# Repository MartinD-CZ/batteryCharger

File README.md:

# AVR-based universal battery charger

**UPDATE!** By popular request, I will be releasing a new version. Check [this post](http://embedblog.eu/?p=204) for more information.  
**UPDATE #2** I've abandoned the project, mostly because of time. What I have so far has been put into the 'unfinished-arduino' folder.

###### Overall
The charger is based on Atmega 328 (because it is dirt cheap) and utilizes its PWM to drive a FET, used as buck converter. There is also an 5110 LCD (again, less than 2 USD on Ebay) to show some basic menus and stuff. Most of the settings are adjustable on the go, so once you build and program it, you can use it without further reprogramming for all battery types and so on.

###### Batteries:
The charger supports all of the most used battery types - that is in my opinion NiCd, NiMH, Li-Ion and SLA. Li-Ion and SLA are charged in constant current-constant voltage mode, while Nickel based batteries are charged with constant current and terminated by about 5 methods (time out, overvoltage, overtemperature, -dV/dT, user termination). I have been using the charger for about a month before posting it here (tested everything except SLA, don’t have those on hand) and everything seems to work seamlessly. Maximum charging current is 3A, maximum charging voltage is almost Vin (that’s about 18V in my setup).

###### Discharge
The charger also comes with a discharge circuitry, used to:
	A) Measure battery capacity
	B) Discharge batteries before charging (useful with NiMH batteries to neutralize their memory effect)
The discharging current is fully adjustable from 0 to 3 amps, with undervoltage protection (again, fully adjustable). There is a small fan, which is automatically switched on when thermal power dissipation is bigger than 2 watts (you can change that, it depends on the size of your heatsink).

###### Power supply
Also in the menu you can find "constant C", "constant V" and "power supply" options. They provide you with simple power supply, useful for SOME applications. Because of the MCU limitations, the transient response time is relatively long, but on loads that do not change quickly, the MCU will react quickly enough. Maximum output voltage of the power supply is almost Vin and output current 3 A.

###### Project
This started as my own personal build, but since I spent a lot of time on it, I decided to publish it. For me, it works well, even for precise charging lithium batteries. 
It is inspired by AVR450, but 99% of the code is my work. I also used 5110 LCD driver library from Radu Motisan, see the 5110 files for credit.
I would like to hear some feedback on this project. What do you think about it? The total cost was less than 10 USD, which, I believe, is dirt cheap. Also, if there will be interest, I am thinking about porting this to STM32, as they are superior to 8-bit AVR and still very cheap. I would also include balancing circuitry. What do you think about that?

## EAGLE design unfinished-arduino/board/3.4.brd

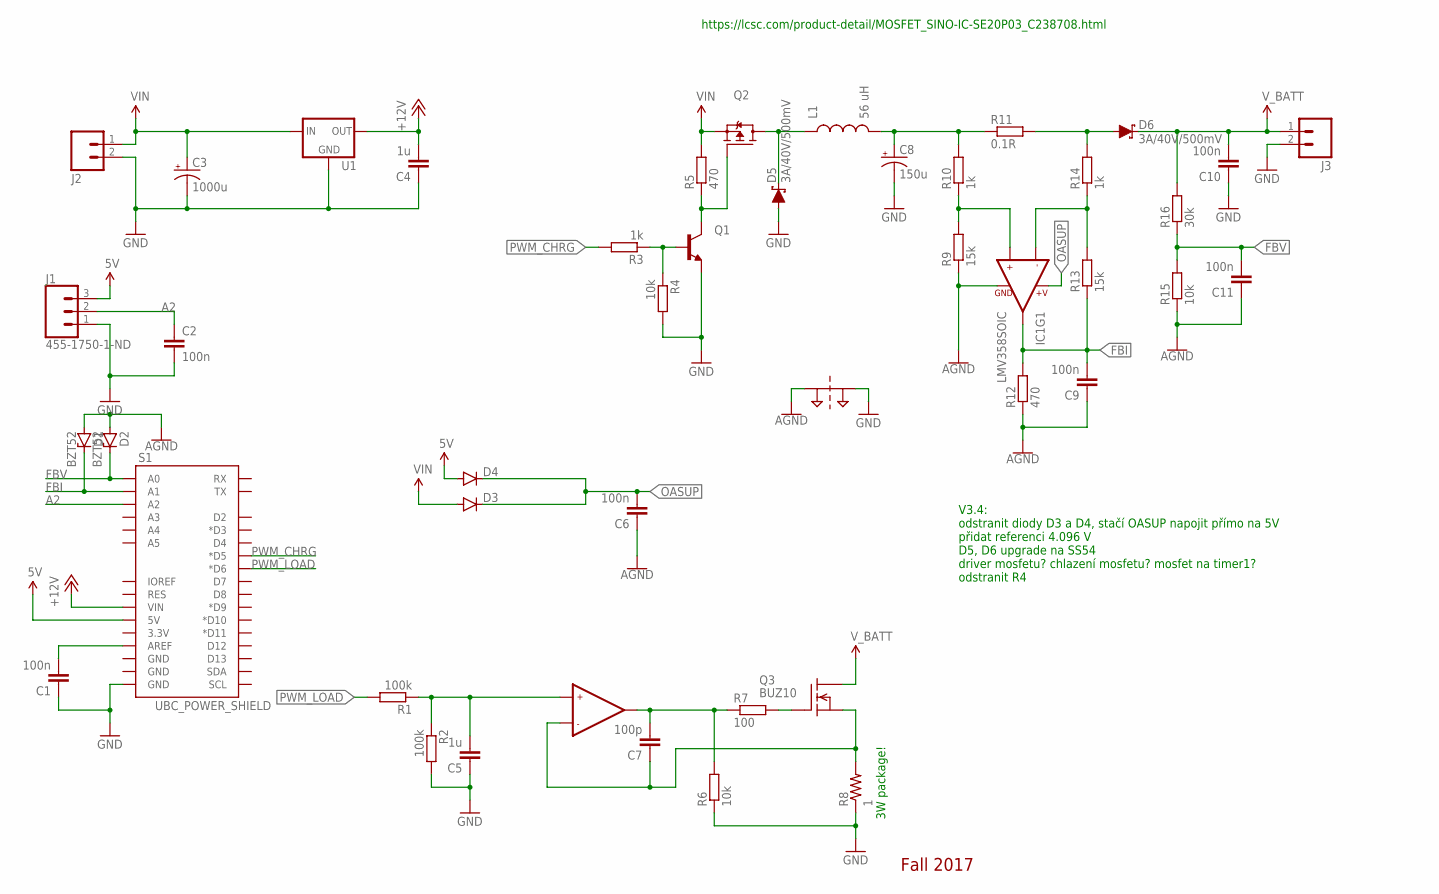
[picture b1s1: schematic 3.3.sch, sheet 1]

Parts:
C1, C2, C6, C9, C10, C11: 100n; C1206
C3: 1000u; CPOL-RADIAL-1000UF-25V
C4, C5: 1u; C1206
C7: 100p; C1206
C8: 150u; CPOL-RADIAL-100UF-25V
D1, D2: BZT52; SOD80C
D3, D4: DIODE-MINIMELF; MINIMELF
D5, D6: 3A/40V/500mV; SMA-DIODE
IC1: LMV358SOIC; SO08
J1: 455-1750-1-ND; 1X03
J2, J3: M025MM; SCREWTERMINAL-5MM-2
L1: 56 uH; CDRH125
PT1: 2PT_GND_TIE
Q1: 2N3904-MMBT; SOT23
Q2: FDD4141TO252; TO252
Q3: BUZ10; TO220
R1, R2: 100k; R1206
R3, R10, R14: 1k; R1206
R4, R6, R15: 10k; R1206
R5, R12: 470; R1206
R7: 100; R1206
R8: 1; 0617/22
R9, R13: 15k; R1206
R11: 0.1R; 0414/15
R16: 30k; R1206
S1: UBC_POWER_SHIELD; UBC_POWER
U1: V_REG_78XXSIDE; 78XXL

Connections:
5V: D4.A, J1.3, S1.5V; also elsewhere on the board
+12V: C4.2, S1.VIN, U1.OUT
A2: C2.1, J1.2, S1.A2
AGND: C6.1, C9.1, C11.1, D1.A, D2.A, IC1.4 (GND), PT1.P$1, R9.1, R12.1, R15.1
FBI: C9.2, D1.C, IC1.1 (OUT1), R12.2, R13.1, S1.A1
FBV: C11.2, D2.C, R15.2, R16.1, S1.A0
GND: C1.1, C2.2, C3.2 (-), C4.1, C5.1, C8.2 (-), C10.1, D5.A, J1.1, J2.2, J3.2, PT1.P$2, Q1.2 (E), R2.2, R4.2, R6.1, R8.1, S1.GND@0 (GND), U1.GND; also elsewhere on the board
unnamed: C8.1 (+), L1.2, R10.2, R11.1
unnamed: C1.2, S1.AREF
unnamed: IC1.3 (+IN1), R9.2, R10.1
unnamed: IC1.2 (-IN1), R13.2, R14.1
unnamed: D5.C, L1.1, Q2.3 (D)
unnamed: D6.A, R11.2, R14.2
unnamed: C7.2, IC1.7 (OUT2), R6.2, R7.1
unnamed: Q1.3 (C), Q2.1 (G), R5.1
unnamed: Q3.1 (G), R7.2
unnamed: C7.1, IC1.6 (-IN2), Q3.3 (S), R8.2
unnamed: C5.2, IC1.5 (+IN2), R1.1, R2.1
unnamed: Q1.1 (B), R3.1, R4.1
OASUP: C6.2, D3.C, D4.C, IC1.8 (+V)
PWM_CHRG: R3.2, S1.D5 (*D5)
PWM_LOAD: R1.2, S1.D6 (*D6)
VIN: C3.1 (+), D3.A, J2.1, Q2.2 (S), R5.2, U1.IN
V_BATT: C10.2, D6.C, J3.1, Q3.2 (D), R16.2

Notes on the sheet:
3W package!
Fall 2017
https://lcsc.com/product-detail/MOSFET_SINO-IC-SE20P03_C238708.html
V3.4: odstranit diody D3 a D4, stačí OASUP napojit přímo na 5V přidat referenci 4.096 V D5, D6 upgrade na SS54 driver mosfetu? chlazení mosfetu? mosfet na timer1? odstranit R4

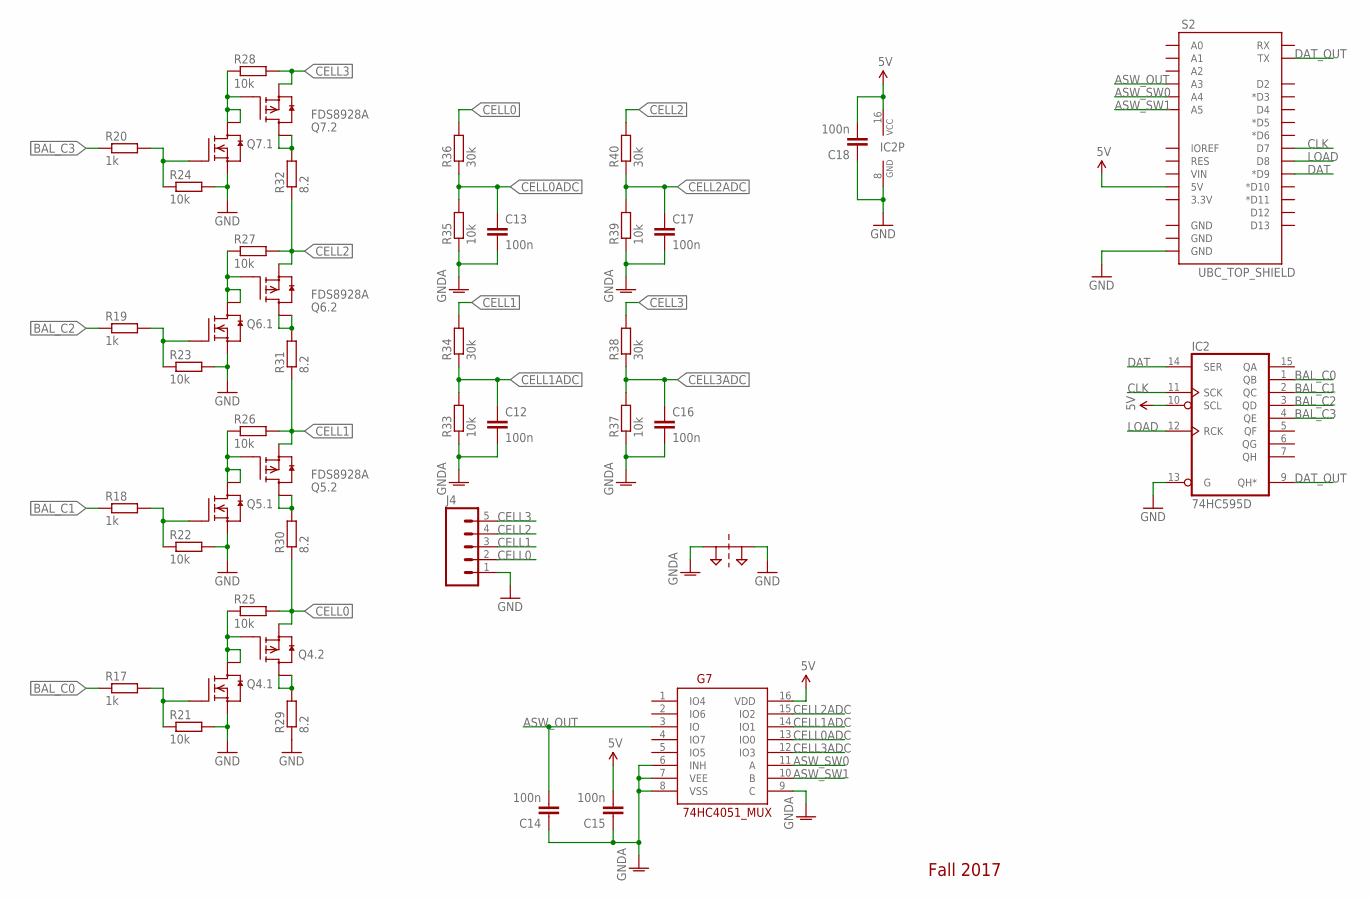
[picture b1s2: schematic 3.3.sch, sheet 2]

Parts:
C12, C13, C14, C15, C16, C17: 100n; C1206
C18: 100n; 1206
G7: 74HC4051_MUX; SO16
IC2: 74HC595D; SO16
J4: M05PTH; 1X05
PT2: 2PT_GND_TIE
Q4, Q5, Q6, Q7: FDS8928A; SO-8
R17, R18, R19, R20: 1k; R1206
R21, R22, R23, R24, R25, R26, R27, R28, R33, R35, R37, R39: 10k; R1206
R29, R30, R31, R32: 8.2; R2512
R34, R36, R38, R40: 30k; R1206
S2: UBC_TOP_SHIELD; UBC_TOP

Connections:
5V: C15.2, C18.2, G7.16 (VDD), IC2.10 (SCL), IC2.16 (VCC), S2.5V; also elsewhere on the board
ASW_OUT: C14.2, G7.3 (IO), S2.A3
ASW_SW0: G7.11 (A), S2.A4
ASW_SW1: G7.10 (B), S2.A5
BAL_C0: IC2.1 (QB), R17.1
BAL_C1: IC2.2 (QC), R18.1
BAL_C2: IC2.3 (QD), R19.1
BAL_C3: IC2.4 (QE), R20.1
CELL0: J4.2, Q4.3 (S), R25.2, R30.1, R36.2
CELL0ADC: C13.1, G7.13 (IO0), R35.2, R36.1
CELL1: J4.3, Q5.3 (S), R26.2, R31.1, R34.2
CELL1ADC: C12.1, G7.14 (IO1), R33.2, R34.1
CELL2: J4.4, Q6.3 (S), R27.2, R32.1, R40.2
CELL2ADC: C17.1, G7.15 (IO2), R39.2, R40.1
CELL3: J4.5, Q7.3 (S), R28.2, R38.2
CELL3ADC: C16.1, G7.12 (IO3), R37.2, R38.1
CLK: IC2.11 (SCK), S2.D7
DAT: IC2.14 (SER), S2.D9 (*D9)
DAT_OUT: IC2.9 (QH*), S2.TX
GND: C18.1, IC2.8 (GND), IC2.13 (G), J4.1, PT2.P$2, Q4.1 (S), Q5.1 (S), Q6.1 (S), Q7.1 (S), R21.2, R22.2, R23.2, R24.2, R29.1, S2.GND@0 (GND); also elsewhere on the board
GNDA: C12.2, C13.2, C14.1, C15.1, C16.2, C17.2, G7.6 (INH), G7.7 (VEE), G7.8 (VSS), G7.9 (C), PT2.P$1, R33.1, R35.1, R37.1, R39.1
LOAD: IC2.12 (RCK), S2.D8
unnamed: Q4.2 (G), R17.2, R21.1
unnamed: Q4.5 (D), Q4.6 (D), R29.2
unnamed: Q5.2 (G), R18.2, R22.1
unnamed: Q5.4 (G), Q5.7 (D), Q5.8 (D), R26.1
unnamed: Q5.5 (D), Q5.6 (D), R30.2
unnamed: Q6.2 (G), R19.2, R23.1
unnamed: Q6.4 (G), Q6.7 (D), Q6.8 (D), R27.1
unnamed: Q6.5 (D), Q6.6 (D), R31.2
unnamed: Q7.2 (G), R20.2, R24.1
unnamed: Q7.4 (G), Q7.7 (D), Q7.8 (D), R28.1
unnamed: Q7.5 (D), Q7.6 (D), R32.2
unnamed: Q4.4 (G), Q4.7 (D), Q4.8 (D), R25.1

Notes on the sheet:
Fall 2017

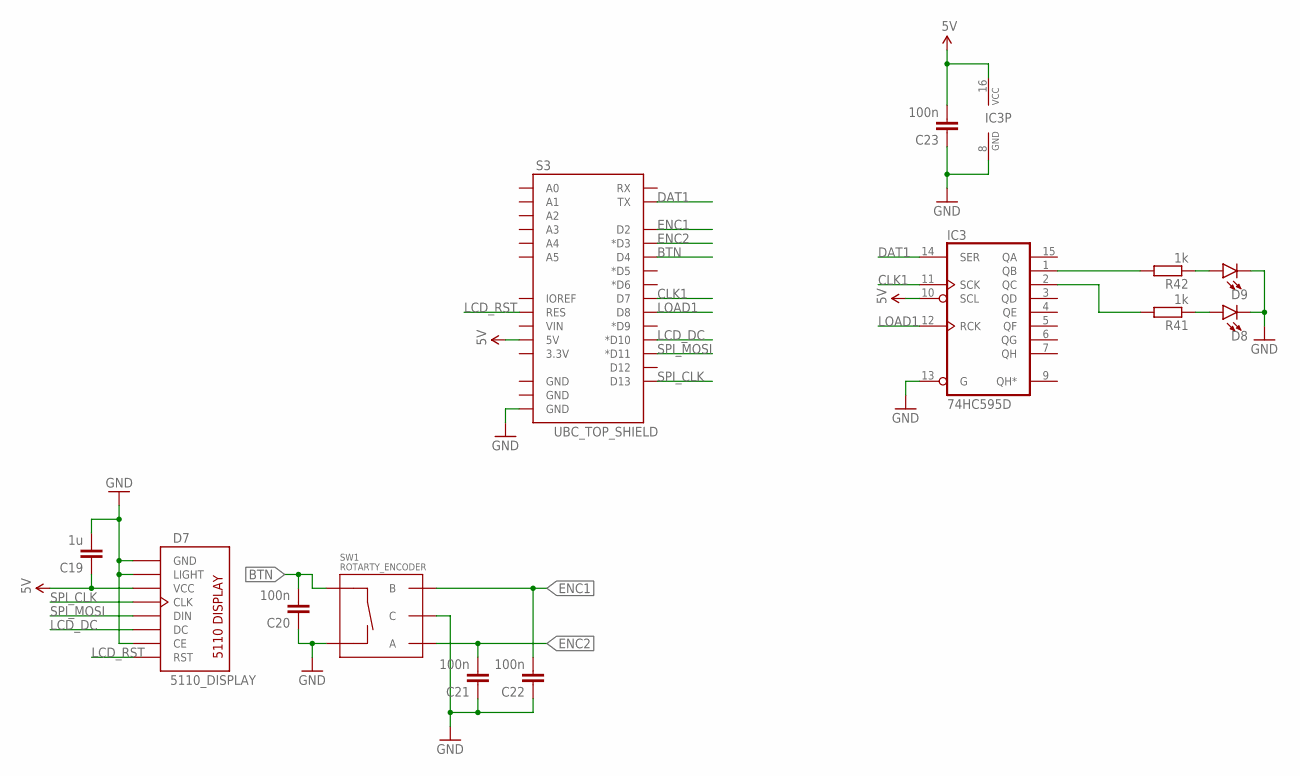
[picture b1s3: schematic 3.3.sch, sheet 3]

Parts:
C19: 1u; 1206
C20, C21, C22, C23: 100n; 1206
D7: 5110_DISPLAY; 5110_LAYOUT
D8, D9: LED5MM; LED_5MM
IC3: 74HC595D; SO16
R41, R42: 1k; R1206
S3: UBC_TOP_SHIELD; UBC_TOP
SW1: ROTARTY_ENCODER; ROTARY_ENC_PLAIN

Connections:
5V: C19.1, C23.2, D7.VCC, IC3.10 (SCL), IC3.16 (VCC), S3.5V; also elsewhere on the board
BTN: C20.2, S3.D4, SW1.SW+
CLK1: IC3.11 (SCK), S3.D7
DAT1: IC3.14 (SER), S3.TX
ENC1: C22.2, S3.D2, SW1.B
ENC2: C21.2, S3.D3 (*D3), SW1.A
GND: C19.2, C20.1, C21.1, C22.1, C23.1, D7.CE, D7.GND, D7.LIGHT, D8.K (C), D9.K (C), IC3.8 (GND), IC3.13 (G), S3.GND@0 (GND), SW1.C, SW1.SW-; also elsewhere on the board
LCD_DC: D7.DC, S3.D10 (*D10)
LCD_RST: D7.RST, S3.RES
LOAD1: IC3.12 (RCK), S3.D8
unnamed: IC3.1 (QB), R42.2
unnamed: IC3.2 (QC), R41.2
unnamed: D9.A, R42.1
unnamed: D8.A, R41.1
SPI_CLK: D7.CLK, S3.D13
SPI_MOSI: D7.DIN, S3.D11 (*D11)

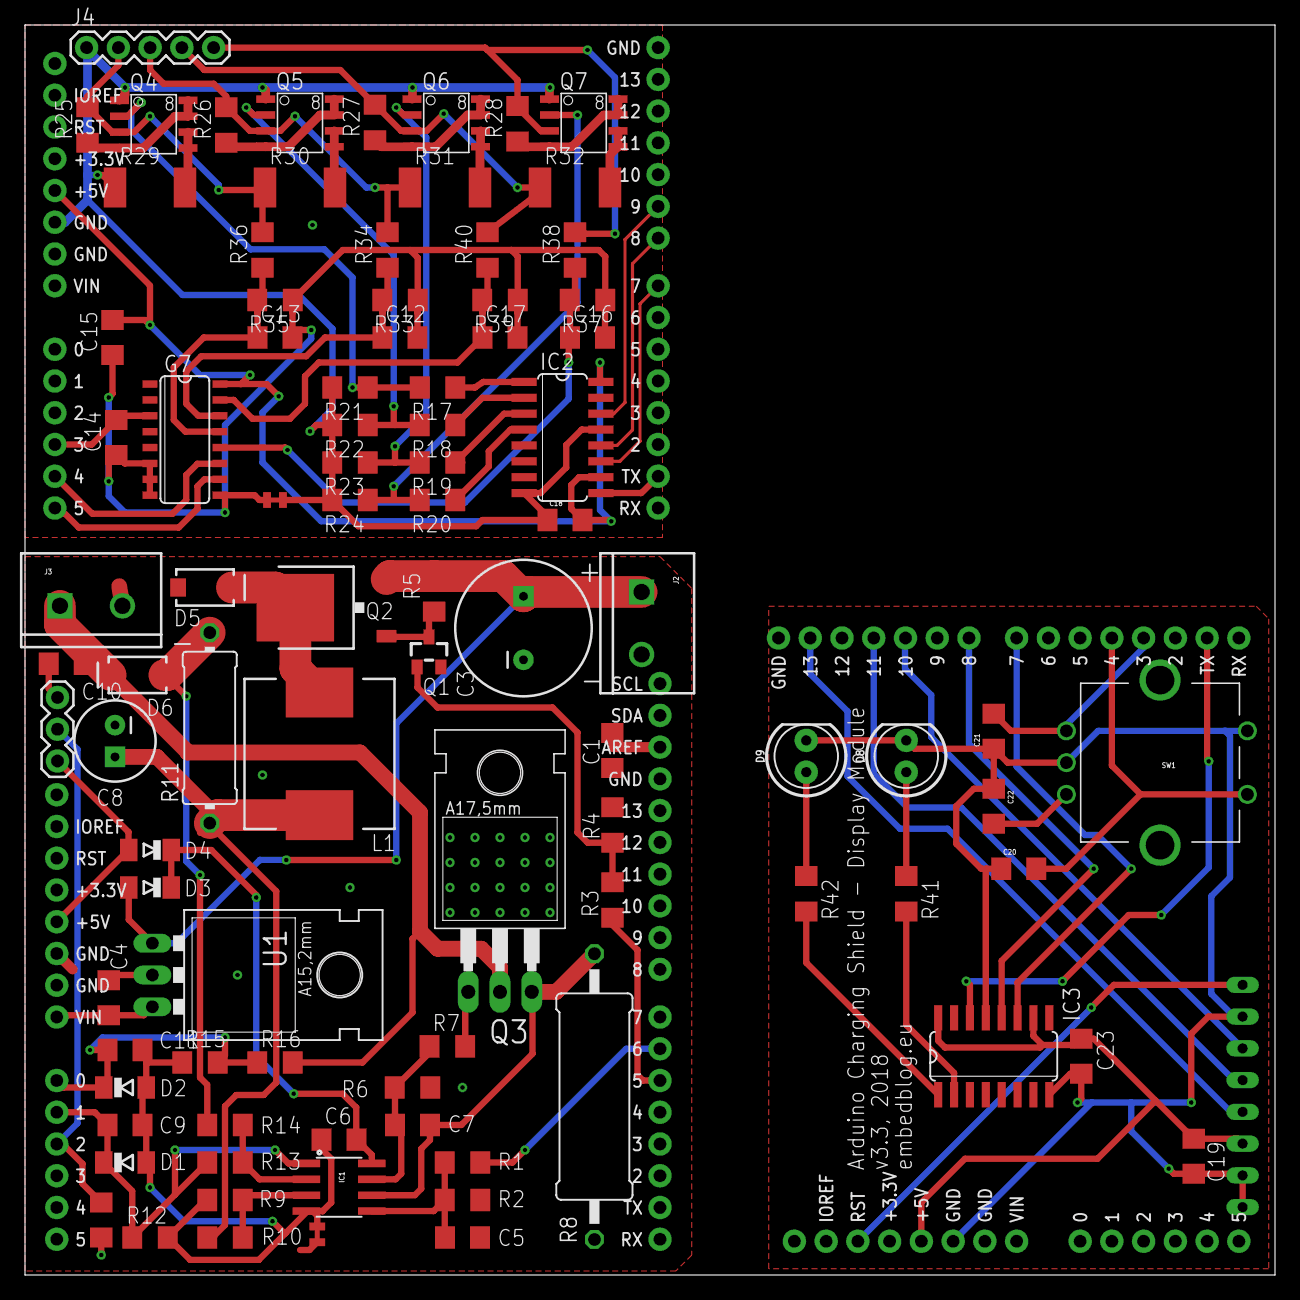
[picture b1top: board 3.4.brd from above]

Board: 2 copper layers, 100.0 x 100.0 mm, 97 parts (0 on the bottom side), 70 nets.

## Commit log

2016-09-05 :lollipop: Added .gitattributes & .gitignore files
2016-09-05 Version 1.1
    As of now, everything is working. The code is not nice (however, it
    could be worse), but works.
2016-09-05 Version 1.1.1
    deleted unnecessary files
2019-03-30 changed readme
    updated with a link to my blog post about a new version
2019-10-19 added experimental
2019-10-19 readme fix

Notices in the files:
parts and their libraries:
SparkFun-Capacitors: Licensing: Creative Commons ShareAlike 4.0 International - https://creativecommons.org/licenses/by-sa/4.0
m-pad-2.1: License : GNU General Public License version 2 (see bottom)
